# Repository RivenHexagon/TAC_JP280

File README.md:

# Total Audio Concepts (TAC) Scorpion Mixing Console Overhaul
## PCB JP280

Redesign of Monitor Connector Card (PCB JP280) in order to populate it with gold
plated Audio Jacks and Molex connectors. The original PCB exceeds the dimensions
of an Eurocard (100 mm x 160 mm) substrate. Luckily it's possible to split it up
into two independet parts, so the layouts can be placed on a copper-plated blank
and etched in a DIY process (see mirrored image of original PCB).

## Made With

I named the new versions JP280C1 & JP280C2 and made them with KiCad 5.1.7. using
a git submodule that handles any special footprints:

https://github.com/RivenHexagon/TAC_KiCad_lib.git

## Further Modifications

The XLR/audio jacks SK1 - SK4 are mounted to the back panel and were then solder
wired to the PCB. The solder connections have now been replaced with 3-pin Molex
connectors.

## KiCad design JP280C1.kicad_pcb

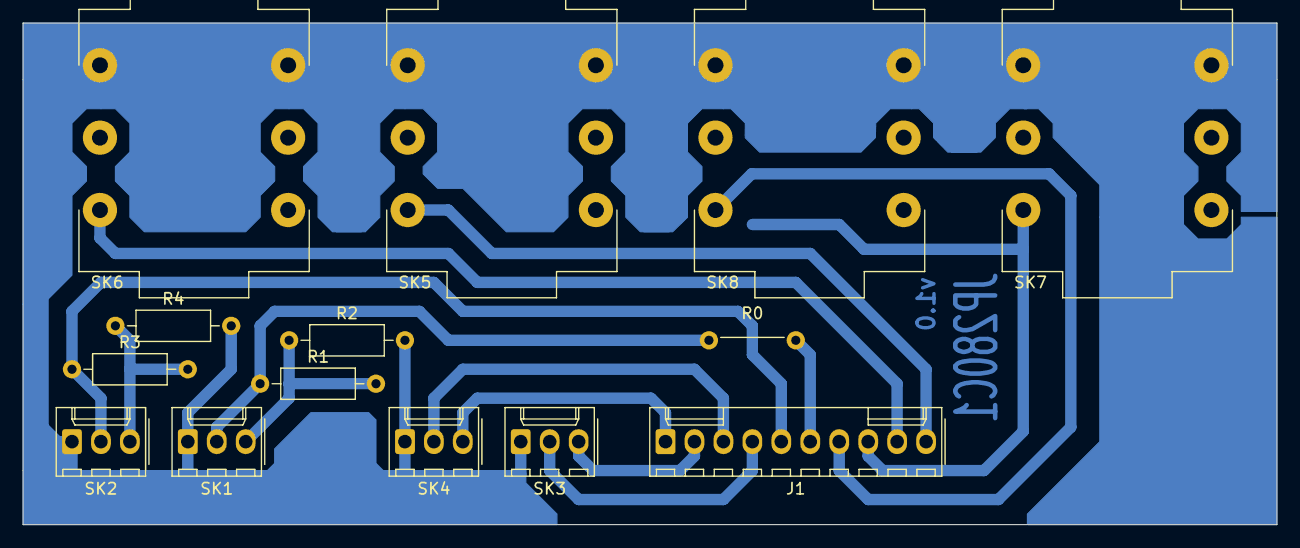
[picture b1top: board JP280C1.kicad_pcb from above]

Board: 2 copper layers, 110.0 x 44.0 mm, 14 parts (0 on the bottom side), 14 nets.

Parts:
J1: Ribbon Cable (C); Molex_KK-254_AE-6410-10A_1x10_P2.54mm_Vertical_reversed
R0: 0R; Wire_Bridge_P7.62mm_Horizontal
R1, R3: 3k; R_Axial_DIN0207_L6.3mm_D2.5mm_P10.16mm_Horizontal
R2, R4: 1k; R_Axial_DIN0207_L6.3mm_D2.5mm_P10.16mm_Horizontal
SK1: Left Bus; Molex_KK-254_AE-6410-03A_1x03_P2.54mm_Vertical_reversed
SK2: Right Bus; Molex_KK-254_AE-6410-03A_1x03_P2.54mm_Vertical_reversed
SK3: Left Insert; Molex_KK-254_AE-6410-03A_1x03_P2.54mm_Vertical_reversed
SK4: Right Insert; Molex_KK-254_AE-6410-03A_1x03_P2.54mm_Vertical_reversed
SK5: Left Monitor; CL13345
SK6: Right Monitor; CL13345
SK7: Left Aux Monitor; CL13345
SK8: Right Aux Monitor; CL13345

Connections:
GND: R2.2, R4.2, SK1.1, SK2.1, SK3.1, SK4.1, SK5.S, SK5.SN, SK6.S, SK6.SN, SK7.S, SK7.SN, SK8.S, SK8.SN
unnamed: J1.1, SK4.3
unnamed: J1.2, SK3.3
unnamed: J1.3, SK4.2
unnamed: J1.4, SK3.2
unnamed: J1.5, R3.1, SK2.2
unnamed: J1.6, R0.2
unnamed: J1.7, SK8.T
unnamed: J1.8, SK7.T
unnamed: J1.9, SK6.T
unnamed: J1.10, SK5.T
unnamed: R0.1, R1.1, SK1.2
unnamed: R1.2, R2.1, SK1.3
unnamed: R3.2, R4.1, SK2.3

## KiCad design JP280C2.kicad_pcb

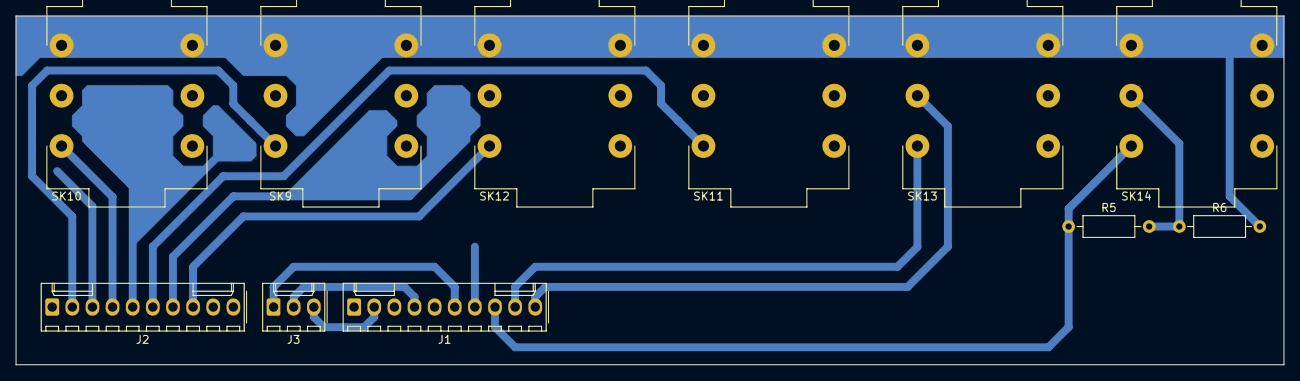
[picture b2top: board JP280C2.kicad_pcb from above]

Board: 2 copper layers, 160.0 x 44.0 mm, 11 parts (0 on the bottom side), 12 nets.

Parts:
J1: Ribbon Cable (A); Molex_KK-254_AE-6410-10A_1x10_P2.54mm_Vertical_reversed
J2: Ribbon Cable (B); Molex_KK-254_AE-6410-10A_1x10_P2.54mm_Vertical_reversed
J3: Meters; Molex_KK-254_AE-6410-03A_1x03_P2.54mm_Vertical_reversed
R5: 10k; R_Axial_DIN0207_L6.3mm_D2.5mm_P10.16mm_Horizontal
R6: 10R; R_Axial_DIN0207_L6.3mm_D2.5mm_P10.16mm_Horizontal
SK9: Left Tape 2; CL13345
SK10: Right Tape 2; CL13345
SK11: Left Tape 1; CL13345
SK12: Right Tape 1; CL13345
SK13: Talkback; CL13345
SK14: OSC; CL13345

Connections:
GND: R6.2, SK9.S, SK9.SN, SK10.S, SK10.SN, SK11.S, SK11.SN, SK12.S, SK12.SN, SK13.S, SK13.SN, SK14.S, SK14.SN
unnamed: J1.2, J3.3
unnamed: J1.4, J3.2
unnamed: J1.6, J3.1
unnamed: J1.8, R5.1, SK14.T
unnamed: J1.9, SK13.T
unnamed: J1.10, SK13.R
unnamed: J2.2, SK9.T
unnamed: J2.4, SK10.T
unnamed: J2.6, SK11.T
unnamed: J2.8, SK12.T
unnamed: R5.2, R6.1, SK14.R

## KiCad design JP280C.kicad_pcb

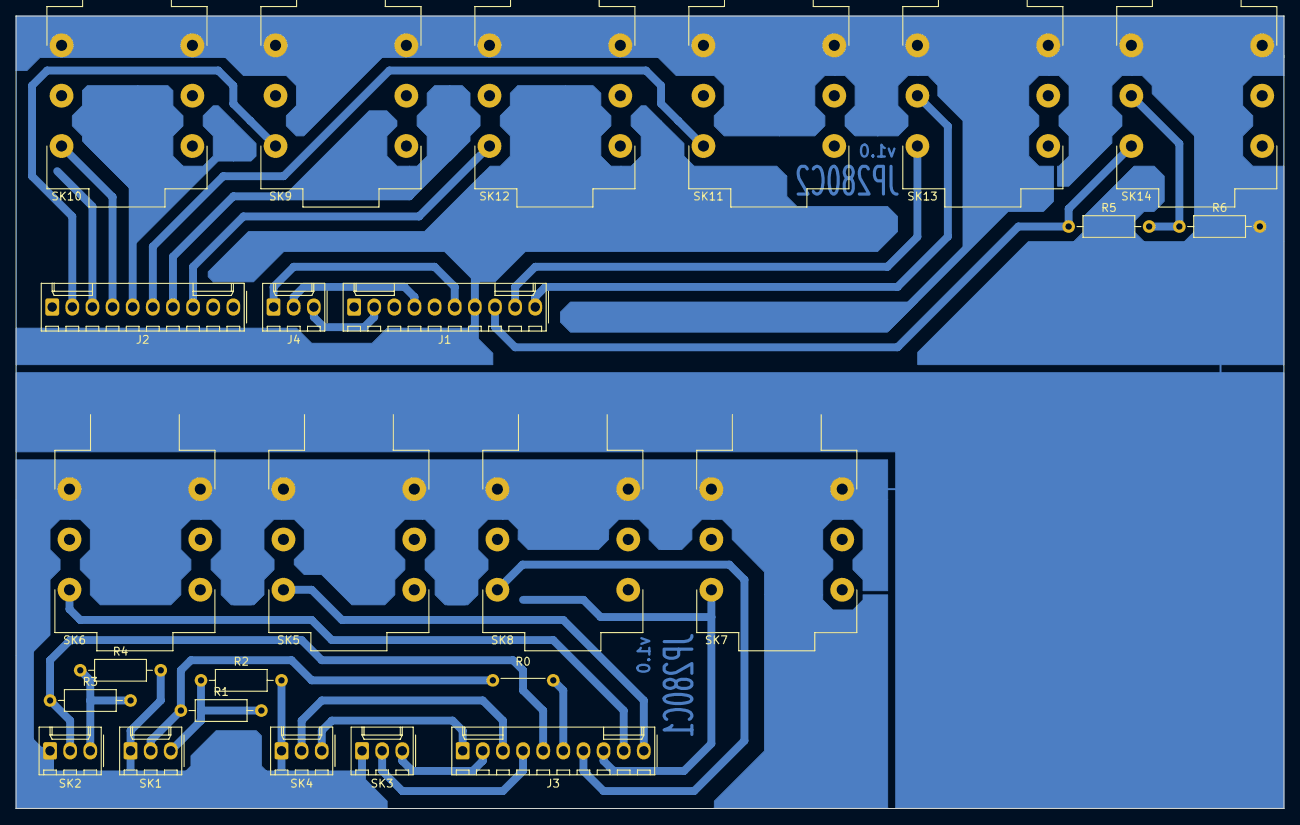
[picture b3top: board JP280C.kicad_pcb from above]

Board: 2 copper layers, 160.0 x 100.0 mm, 25 parts (0 on the bottom side), 25 nets.

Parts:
J1: Ribbon Cable (A); Molex_KK-254_AE-6410-10A_1x10_P2.54mm_Vertical_reversed
J2: Ribbon Cable (B); Molex_KK-254_AE-6410-10A_1x10_P2.54mm_Vertical_reversed
J3: Ribbon Cable (C); Molex_KK-254_AE-6410-10A_1x10_P2.54mm_Vertical_reversed
J4: Meters; Molex_KK-254_AE-6410-03A_1x03_P2.54mm_Vertical_reversed
R0: 0R; Wire_Bridge_P7.62mm_Horizontal
R1, R3: 3k; R_Axial_DIN0207_L6.3mm_D2.5mm_P10.16mm_Horizontal
R2, R4: 1k; R_Axial_DIN0207_L6.3mm_D2.5mm_P10.16mm_Horizontal
R5: 10k; R_Axial_DIN0207_L6.3mm_D2.5mm_P10.16mm_Horizontal
R6: 10R; R_Axial_DIN0207_L6.3mm_D2.5mm_P10.16mm_Horizontal
SK1: Left Bus; Molex_KK-254_AE-6410-03A_1x03_P2.54mm_Vertical_reversed
SK2: Right Bus; Molex_KK-254_AE-6410-03A_1x03_P2.54mm_Vertical_reversed
SK3: Left Insert; Molex_KK-254_AE-6410-03A_1x03_P2.54mm_Vertical_reversed
SK4: Right Insert; Molex_KK-254_AE-6410-03A_1x03_P2.54mm_Vertical_reversed
SK5: Left Monitor; CL13345
SK6: Right Monitor; CL13345
SK7: Left Aux Monitor; CL13345
SK8: Right Aux Monitor; CL13345
SK9: Left Tape 2; CL13345
SK10: Right Tape 2; CL13345
SK11: Left Tape 1; CL13345
SK12: Right Tape 1; CL13345
SK13: Talkback; CL13345
SK14: OSC; CL13345

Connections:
GND: R2.2, R4.2, R6.2, SK1.1, SK2.1, SK3.1, SK4.1, SK5.S, SK5.SN, SK6.S, SK6.SN, SK7.S, SK7.SN, SK8.S, SK8.SN, SK9.S, SK9.SN, SK10.S, SK10.SN, SK11.S, SK11.SN, SK12.S, SK12.SN, SK13.S, SK13.SN, SK14.S, SK14.SN
unnamed: J1.2, J4.3
unnamed: J1.4, J4.2
unnamed: J1.6, J4.1
unnamed: J1.8, R5.1, SK14.T
unnamed: J1.9, SK13.T
unnamed: J1.10, SK13.R
unnamed: J2.2, SK9.T
unnamed: J2.4, SK10.T
unnamed: J2.6, SK11.T
unnamed: J2.8, SK12.T
unnamed: J3.1, SK4.3
unnamed: J3.2, SK3.3
unnamed: J3.3, SK4.2
unnamed: J3.4, SK3.2
unnamed: J3.5, R3.1, SK2.2
unnamed: J3.6, R0.2
unnamed: J3.7, SK8.T
unnamed: J3.8, SK7.T
unnamed: J3.9, SK6.T
unnamed: J3.10, SK5.T
unnamed: R0.1, R1.1, SK1.2
unnamed: R1.2, R2.1, SK1.3
unnamed: R3.2, R4.1, SK2.3
unnamed: R5.2, R6.1, SK14.R

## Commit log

2020-11-23 empty project for board 1/2 (110x44)
2020-11-23 wiring done for board 1/2
2020-11-26 footprints assigned
2020-11-26 placed Audio Jacks horizontally on metirc grid
2020-11-26 completed wiring
2020-11-26 updated footprint 3d model and flipped copper
2020-11-26 corrected placement of SK7 and SK8
2020-11-27 preparing to add libs as submodule
2020-11-27 added libraries as submodule
2020-11-27 added README
2020-11-27 replaced vias with wire bridge
2020-11-27 added copper fill
2020-11-28 readme update
2020-11-29 schematic done for JP280C2
2020-11-29 PBC wiring complete
2020-11-29 part of copper pour
2020-11-29 completed copper pour
2020-11-30 lib update
2020-12-10 merged both PCBs into one project JP280C and arranged them on a 160 mm x 100 mm Eurocard substrate
2020-12-10 narrowed JP208C1 to 107 mm; added engravings to Cmts.User layer
